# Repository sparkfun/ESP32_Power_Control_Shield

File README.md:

ESP32 Thing Power Control Shield
=======

*[SparkFun ESP32 Thing Power Control Shield](https://www.sparkfun.com/products/14155)*

The ESP32 Thing Power Control Shield is a small adapter board for the [ESP32 Thing](https://www.sparkfun.com/products/13907). The shield gives the ESP32 Thing the power to switch loads of up to 5A between 5 and 28VDC. The shield has 6 output pins to connect loads to, and three current sensors connected to outputs 2, 4, and 6. Operational amplifiers are by default configured as voltage followers, but feedback resistors are broken out to increase the gain of the non-inverting op-amp, which allows for greater precision depending on the maximum expected loads. 

Repository Contents
-------------------

* **/Production** - Panelized version of the design for production
* **/Hardware** - All Eagle design files (.brd, .sch)

License Information
-------------------

This design is [OSHW](http://www.oshwa.org/definition/) and public domain but you buy me a beer if you use this and we meet someday ([Beerware license](http://en.wikipedia.org/wiki/Beerware)).

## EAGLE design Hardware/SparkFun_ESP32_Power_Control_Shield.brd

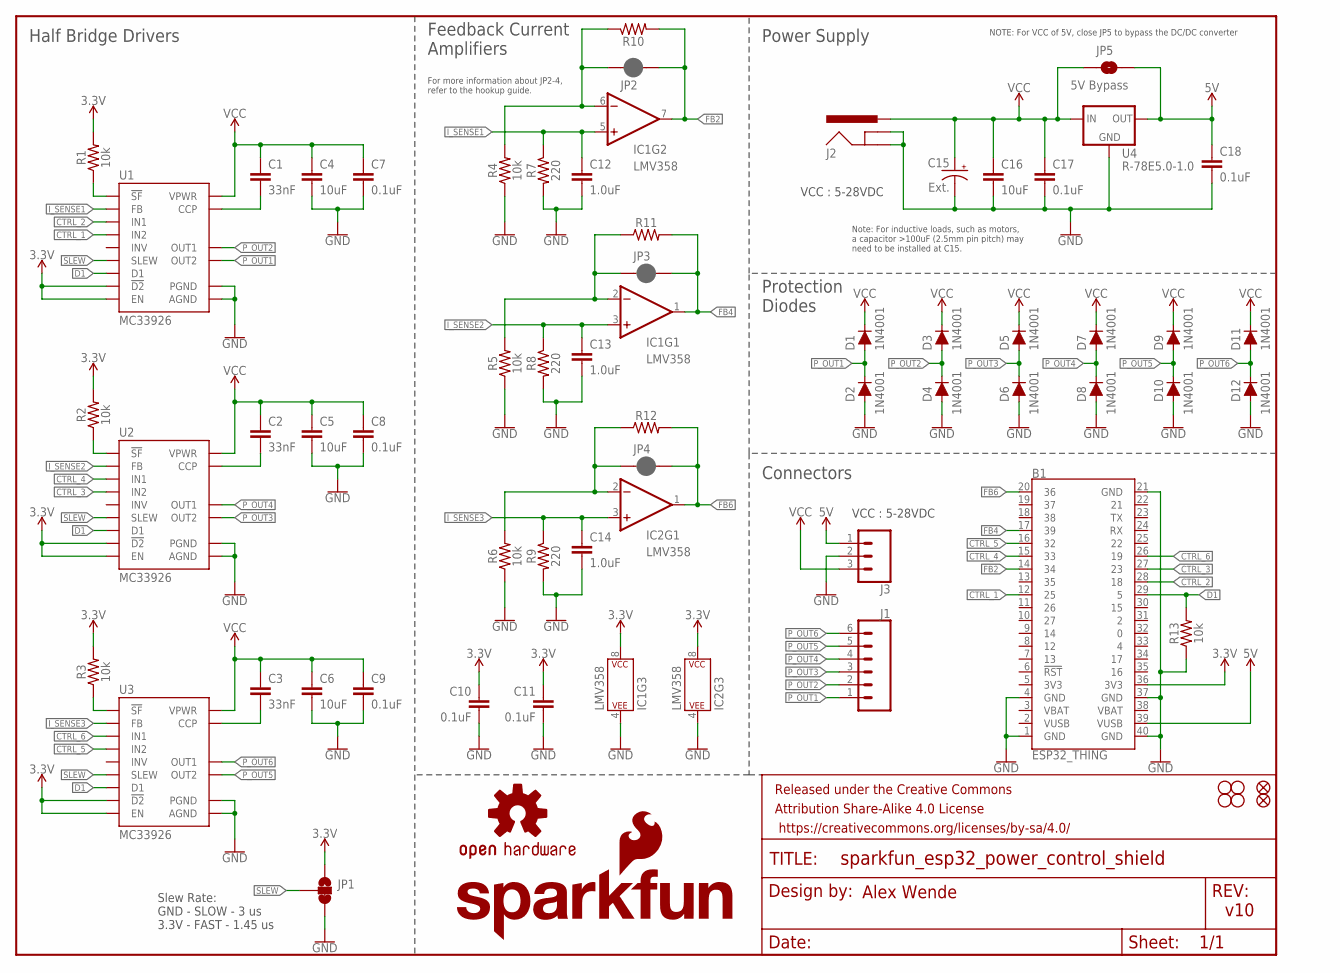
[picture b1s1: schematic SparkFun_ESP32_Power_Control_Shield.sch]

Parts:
B1: ESP32_THING
C1, C2, C3: 33nF; 0603
C4, C5, C6, C16: 10uF; 1210
C7, C8, C9, C10, C11, C17, C18: 0.1uF; 0603
C12, C13, C14: 1.0uF; 0603
C15: Ext.; CPOL-RADIAL-2.5MM-6.5MM
D1, D2, D3, D4, D5, D6, D7, D8, D9, D10, D11, D12: 1N4001; DIODE-1N4001
FD1, FD2: FIDUCIALUFIDUCIAL; FIDUCIAL-MICRO
FRAME1: FRAME-LETTER; CREATIVE_COMMONS
H1, H2, H3, H4: STAND-OFF
IC1, IC2: LMV358; SO08
J1: CONN_063.5MM-6; SCREWTERMINAL-3.5MM-6
J2: POWER_JACKPTH_LOCK; POWER_JACK_PTH_LOCK
J3: CONN_03SCREW; SCREWTERMINAL-3.5MM-3
JP1: JUMPER-SMT_3_1-NC_TRACE_SILK; SMT-JUMPER_3_1-NC_TRACE_SILK
JP2, JP3, JP4: JUMPER-SMT_2_NC_PASTE_NO-SILK; SMT-JUMPER_2_NC_PASTE_NO-SILK
JP5: 5V Bypass; SMT-JUMPER_2_NO_SILK
LOGO1: SFE_LOGO_NAME_FLAME.2_INCH; SFE_LOGO_NAME_FLAME_.2
LOGO2: OSHW-LOGOM; OSHW-LOGO-M
R1, R2, R3, R4, R5, R6, R13: 10k; 0603
R7, R8, R9: 220; 0603
R10, R11, R12: 1KOHM-HORIZ-1/4W-1%; AXIAL-0.3
U1, U2, U3: MC33926; 32-PQFN
U4: R-78E5.0-1.0; DC-DC_CONVERTER_78XX

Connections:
3.3V: B1.36 (3V3), C10.1, C11.1, IC1.8 (P$V+), IC2.8 (P$V+), JP1.1, R1.2, R2.2, R3.2, U1.P$10 (EN), U1.P$16 (!D2), U2.P$10 (EN), U2.P$16 (!D2), U3.P$10 (EN), U3.P$16 (!D2)
5V: B1.39 (VUSB), C18.1, J3.1, JP5.2, U4.VOUT (OUT)
CTRL_1: B1.12 (25), U1.P$1 (IN2)
CTRL_2: B1.28 (18), U1.P$2 (IN1)
CTRL_3: B1.27 (23), U2.P$1 (IN2)
CTRL_4: B1.15 (33), U2.P$2 (IN1)
CTRL_5: B1.16 (32), U3.P$1 (IN2)
CTRL_6: B1.26 (19), U3.P$2 (IN1)
D1: B1.29 (5), R13.2, U1.P$26 (D1), U2.P$26 (D1), U3.P$26 (D1)
FB2: B1.14 (34), IC1.7 (OUT), JP2.2, R10.P$2 (2)
FB4: B1.17 (39), IC1.1 (OUT), JP3.2, R11.P$2 (2)
FB6: B1.20 (36), IC2.1 (OUT), JP4.2, R12.P$2 (2)
GND: B1.1 (GND), B1.4 (GND), B1.21 (GND), B1.37 (GND), B1.40 (GND), C4.2, C5.2, C6.2, C7.2, C8.2, C9.2, C10.2, C11.2, C12.2, C13.2, C14.2, C15.2 (-), C16.2, C17.2, C18.2, D2.A, D4.A, D6.A, D8.A, D10.A, D12.A, IC1.4 (P$V-), IC2.4 (P$V-), J2.GND, J2.GNDBREAK, J3.2, JP1.3, R4.1, R5.1, R6.1, R7.2, R8.2, R9.2, R13.1, U1.P$5 (AGND), U1.P$18 (PGND), U1.P$19 (PGND), U1.P$20 (PGND), U1.P$22 (PGND), U1.P$23 (PGND), U1.P$24 (PGND), U1.P$33 (AGND), U2.P$5 (AGND), U2.P$18 (PGND), U2.P$19 (PGND), U2.P$20 (PGND), U2.P$22 (PGND), U2.P$23 (PGND), U2.P$24 (PGND), U2.P$33 (AGND), U3.P$5 (AGND), U3.P$18 (PGND), U3.P$19 (PGND), U3.P$20 (PGND), U3.P$22 (PGND), U3.P$23 (PGND), U3.P$24 (PGND), U3.P$33 (AGND), U4.GND
I_SENSE1: C12.1, IC1.5 (+IN), R7.1, U1.P$8 (FB)
I_SENSE2: C13.1, IC1.3 (+IN), R8.1, U2.P$8 (FB)
I_SENSE3: C14.1, IC2.3 (+IN), R9.1, U3.P$8 (FB)
unnamed: IC1.6 (-IN), JP2.1, R4.2, R10.P$1 (1)
unnamed: IC2.2 (-IN), JP4.1, R6.2, R12.P$1 (1)
unnamed: IC1.2 (-IN), JP3.1, R5.2, R11.P$1 (1)
unnamed: R2.1, U2.P$21 (!SF)
unnamed: C2.2, U2.P$32 (CCP)
unnamed: R3.1, U3.P$21 (!SF)
unnamed: R1.1, U1.P$21 (!SF)
unnamed: C1.2, U1.P$32 (CCP)
unnamed: C3.2, U3.P$32 (CCP)
P_OUT1: D1.A, D2.C, J1.1, U1.P$27 (OUT2), U1.P$28 (OUT2), U1.P$29 (OUT2), U1.P$30 (OUT2)
P_OUT2: D3.A, D4.C, J1.2, U1.P$12 (OUT1), U1.P$13 (OUT1), U1.P$14 (OUT1), U1.P$15 (OUT1)
P_OUT3: D5.A, D6.C, J1.3, U2.P$27 (OUT2), U2.P$28 (OUT2), U2.P$29 (OUT2), U2.P$30 (OUT2)
P_OUT4: D7.A, D8.C, J1.4, U2.P$12 (OUT1), U2.P$13 (OUT1), U2.P$14 (OUT1), U2.P$15 (OUT1)
P_OUT5: D9.A, D10.C, J1.5, U3.P$27 (OUT2), U3.P$28 (OUT2), U3.P$29 (OUT2), U3.P$30 (OUT2)
P_OUT6: D11.A, D12.C, J1.6, U3.P$12 (OUT1), U3.P$13 (OUT1), U3.P$14 (OUT1), U3.P$15 (OUT1)
SLEW: JP1.2, U1.P$3 (SLEW), U2.P$3 (SLEW), U3.P$3 (SLEW)
VCC: C1.1, C2.1, C3.1, C4.1, C5.1, C6.1, C7.1, C8.1, C9.1, C15.1 (+), C16.1, C17.1, D1.C, D3.C, D5.C, D7.C, D9.C, D11.C, J2.PWR, J3.3, JP5.1, U1.P$4 (VPWR), U1.P$6 (VPWR), U1.P$11 (VPWR), U1.P$31 (VPWR), U2.P$4 (VPWR), U2.P$6 (VPWR), U2.P$11 (VPWR), U2.P$31 (VPWR), U3.P$4 (VPWR), U3.P$6 (VPWR), U3.P$11 (VPWR), U3.P$31 (VPWR), U4.VIN (IN)

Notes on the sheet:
Alex Wende
v10
Half Bridge Drivers
Feedback Current Amplifiers
Power Supply
Protection Diodes
Connectors
Slew Rate: GND - SLOW - 3 us 3.3V - FAST - 1.45 us
VCC : 5-28VDC
NOTE: For VCC of 5V, close JP5 to bypass the DC/DC converter
For more information about JP2-4, refer to the hookup guide.
Note: For inductive loads, such as motors, a capacitor >100uF (2.5mm pin pitch) may need to be installed at C15.

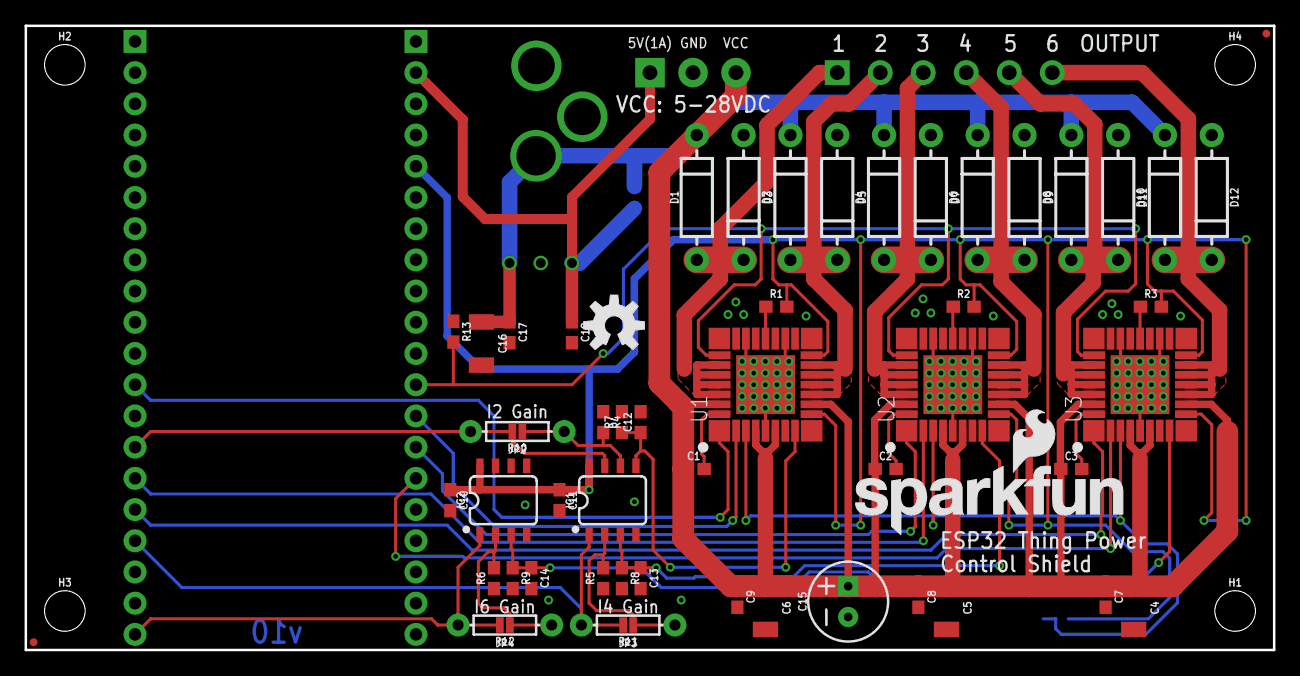
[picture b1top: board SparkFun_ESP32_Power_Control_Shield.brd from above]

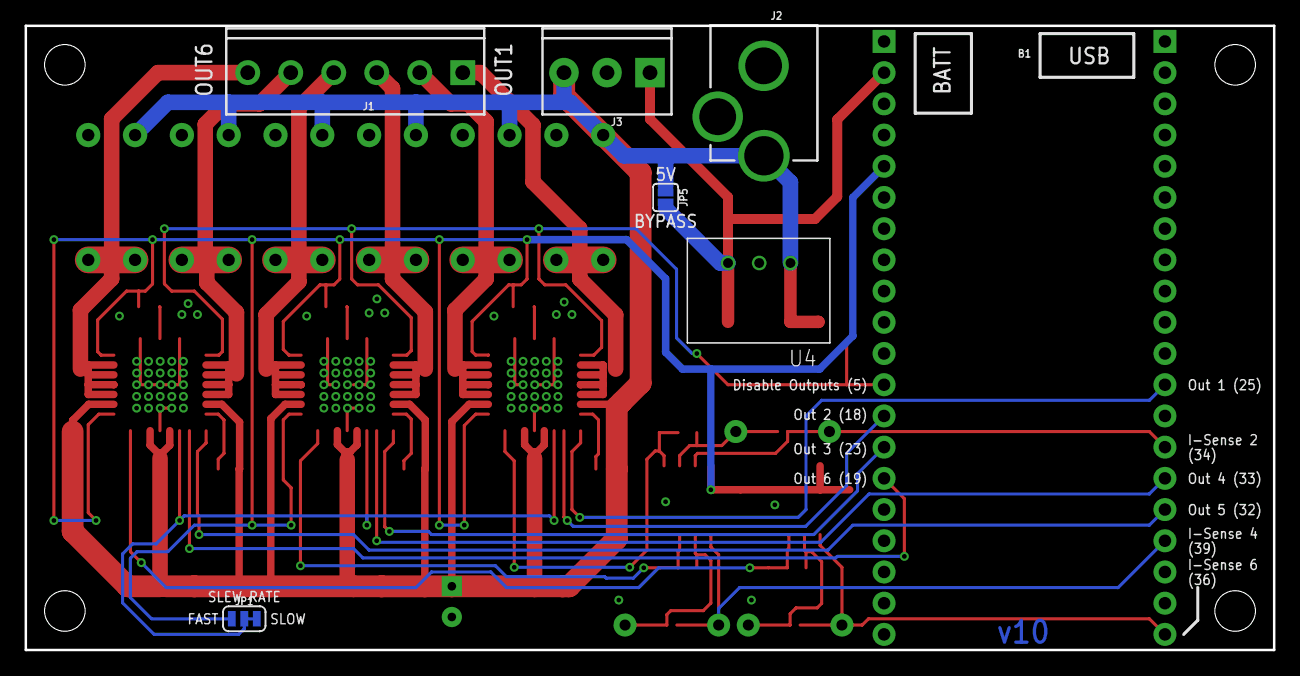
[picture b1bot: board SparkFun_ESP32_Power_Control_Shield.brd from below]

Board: 2 copper layers, 101.6 x 50.8 mm, 68 parts (7 on the bottom side), 33 nets.

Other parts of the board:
U$1: ORDERING_INSTRUCTIONS

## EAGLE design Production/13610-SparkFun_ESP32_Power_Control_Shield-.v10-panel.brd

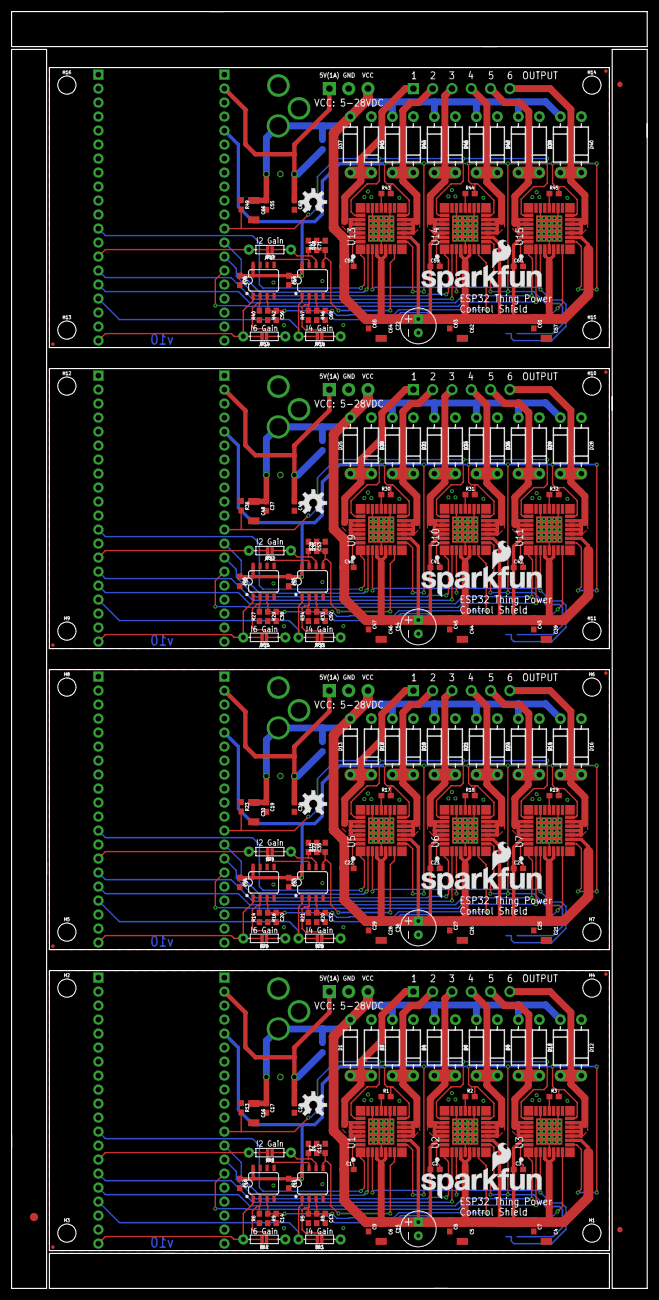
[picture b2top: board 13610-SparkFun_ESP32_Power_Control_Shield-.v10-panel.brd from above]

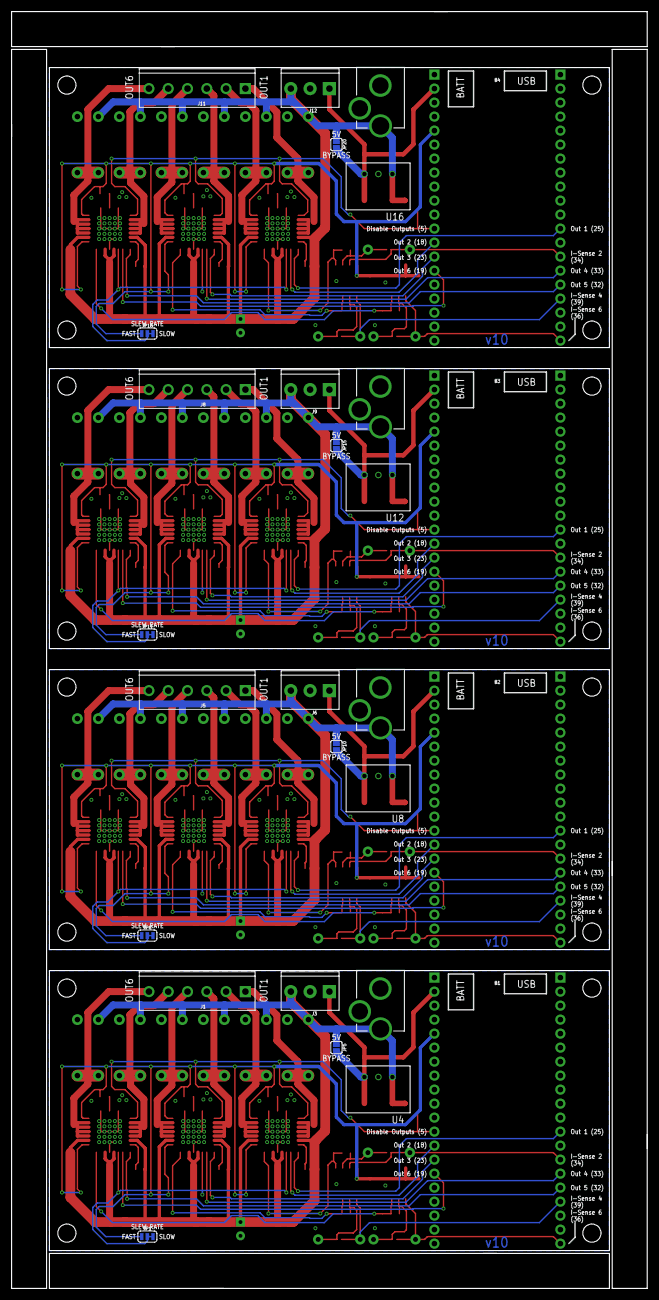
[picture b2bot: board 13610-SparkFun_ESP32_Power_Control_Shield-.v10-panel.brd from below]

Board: 2 copper layers, 115.3 x 231.6 mm, 267 parts (28 on the bottom side), 132 nets.

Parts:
B1, B2, B3, B4: ESP32_THING
C1, C2, C3, C22, C23, C24, C40, C41, C42, C58, C59, C60: 33nF; 0603
C4, C5, C6, C16, C21, C26, C28, C30, C39, C44, C46, C48, C57, C62, C64, C66: 10uF; 1210
C7, C8, C9, C10, C11, C17, C18, C19, C25, C27, C29, C31, C33, C34, C37, C43, C45, C47, C49, C51, C52, C55, C61, C63, C65, C67, C69, C70: 0.1uF; 0603
C12, C13, C14, C20, C32, C35, C38, C50, C53, C56, C68, C71: 1.0uF; 0603
C15, C36, C54, C72: Ext.; CPOL-RADIAL-2.5MM-6.5MM
D1, D2, D3, D4, D5, D6, D7, D8, D9, D10, D11, D12, D13, D14, D15, D16, D17, D18, D19, D20, D21, D22, D23, D24, D25, D26, D27, D28, D29, D30, D31, D32, D33, D34, D35, D36, D37, D38, D39, D40, D41, D42, D43, D44, D45, D46, D47, D48: 1N4001; DIODE-1N4001
E$1: FIDUCIAL-1.5X3
E$7, E$8: FIDUCIAL-1X2
FD1, FD2, FD3, FD4, FD5, FD6, FD7, FD8: FIDUCIALUFIDUCIAL; FIDUCIAL-MICRO
H1, H2, H3, H4, H5, H6, H7, H8, H9, H10, H11, H12, H13, H14, H15, H16: STAND-OFF
IC1, IC2, IC3, IC4, IC5, IC6, IC7, IC8: LMV358; SO08
J1, J5, J8, J11: SCREWTERMINAL-3.5MM-6
J2, J4, J7, J10: POWER_JACKPTH_LOCK; POWER_JACK_PTH_LOCK
J3, J6, J9, J12: SCREWTERMINAL-3.5MM-3
JP1, JP6, JP11, JP16: SMT-JUMPER_3_1-NC_TRACE_SILK
JP2, JP3, JP4, JP7, JP8, JP9, JP12, JP13, JP14, JP17, JP18, JP19: SMT-JUMPER_2_NC_PASTE_NO-SILK
JP5, JP10, JP15, JP20: 5V Bypass; SMT-JUMPER_2_NO_SILK
LOGO1, LOGO3, LOGO5, LOGO7: SFE_LOGO_NAME_FLAME.2_INCH; SFE_LOGO_NAME_FLAME_.2
LOGO2, LOGO4, LOGO6, LOGO8: OSHW-LOGOM; OSHW-LOGO-M
R1, R2, R3, R4, R5, R6, R13, R14, R17, R18, R19, R21, R22, R23, R27, R30, R31, R32, R34, R35, R36, R40, R43, R44, R45, R47, R48, R49: 10k; 0603
R7, R8, R9, R15, R16, R20, R28, R29, R33, R41, R42, R46: 220; 0603
R10, R11, R12, R24, R25, R26, R37, R38, R39, R50, R51, R52: AXIAL-0.3
U1, U2, U3, U5, U6, U7, U9, U10, U11, U13, U14, U15: MC33926; 32-PQFN
U4, U8, U12, U16: R-78E5.0-1.0; DC-DC_CONVERTER_78XX

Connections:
3.3V: B1.36, C10.1, C11.1, IC1.8, IC2.8, JP1.1, R1.2, R2.2, R3.2, U1.P$10, U1.P$16, U2.P$10, U2.P$16, U3.P$10, U3.P$16
3.3V1: B2.36, C33.1, C34.1, IC3.8, IC4.8, JP6.1, R17.2, R18.2, R19.2, U5.P$10, U5.P$16, U6.P$10, U6.P$16, U7.P$10, U7.P$16
3.3V2: B3.36, C51.1, C52.1, IC5.8, IC6.8, JP11.1, R30.2, R31.2, R32.2, U9.P$10, U9.P$16, U10.P$10, U10.P$16, U11.P$10, U11.P$16
3.3V3: B4.36, C69.1, C70.1, IC7.8, IC8.8, JP16.1, R43.2, R44.2, R45.2, U13.P$10, U13.P$16, U14.P$10, U14.P$16, U15.P$10, U15.P$16
5V: B1.39, C18.1, J3.1, JP5.2, U4.VOUT
5V1: B2.39, C31.1, J6.1, JP10.2, U8.VOUT
5V2: B3.39, C49.1, J9.1, JP15.2, U12.VOUT
5V3: B4.39, C67.1, J12.1, JP20.2, U16.VOUT
CTRL_1: B1.12, U1.P$1
CTRL_2: B1.28, U1.P$2
CTRL_3: B1.27, U2.P$1
CTRL_4: B1.15, U2.P$2
CTRL_5: B1.16, U3.P$1
CTRL_6: B1.26, U3.P$2
CTRL_7: B2.26, U7.P$2
CTRL_8: B2.16, U7.P$1
CTRL_9: B2.15, U6.P$2
CTRL_10: B2.27, U6.P$1
CTRL_11: B2.28, U5.P$2
CTRL_12: B2.12, U5.P$1
CTRL_13: B3.26, U11.P$2
CTRL_14: B3.16, U11.P$1
CTRL_15: B3.15, U10.P$2
CTRL_16: B3.27, U10.P$1
CTRL_17: B3.28, U9.P$2
CTRL_18: B3.12, U9.P$1
CTRL_19: B4.26, U15.P$2
CTRL_20: B4.16, U15.P$1
CTRL_21: B4.15, U14.P$2
CTRL_22: B4.27, U14.P$1
CTRL_23: B4.28, U13.P$2
CTRL_24: B4.12, U13.P$1
D1: B1.29, R13.2, U1.P$26, U2.P$26, U3.P$26
D2: B2.29, R23.2, U5.P$26, U6.P$26, U7.P$26
D3: B3.29, R36.2, U9.P$26, U10.P$26, U11.P$26
D4: B4.29, R49.2, U13.P$26, U14.P$26, U15.P$26
FB1: B2.20, IC4.1, JP9.2, R26.P$2
FB2: B1.14, IC1.7, JP2.2, R10.P$2
FB3: B2.17, IC3.1, JP8.2, R25.P$2
FB4: B1.17, IC1.1, JP3.2, R11.P$2
FB5: B2.14, IC3.7, JP7.2, R24.P$2
FB6: B1.20, IC2.1, JP4.2, R12.P$2
FB7: B3.20, IC6.1, JP14.2, R39.P$2
FB8: B3.17, IC5.1, JP13.2, R38.P$2
FB9: B3.14, IC5.7, JP12.2, R37.P$2
FB10: B4.20, IC8.1, JP19.2, R52.P$2
FB11: B4.17, IC7.1, JP18.2, R51.P$2
FB12: B4.14, IC7.7, JP17.2, R50.P$2
GND: B1.1, B1.4, B1.21, B1.37, B1.40, C4.2, C5.2, C6.2, C7.2, C8.2, C9.2, C10.2, C11.2, C12.2, C13.2, C14.2, C15.2, C16.2, C17.2, C18.2, D2.A, D4.A, D6.A, D8.A, D10.A, D12.A, IC1.4, IC2.4, J2.GND, J2.GNDBREAK, J3.2, JP1.3, R4.1, R5.1, R6.1, R7.2, R8.2, R9.2, R13.1, U1.P$5, U1.P$18, U1.P$19, U1.P$20, U1.P$22, U1.P$23, U1.P$24, U1.P$33, U2.P$5, U2.P$18, U2.P$19, U2.P$20, U2.P$22, U2.P$23, U2.P$24, U2.P$33, U3.P$5, U3.P$18, U3.P$19, U3.P$20, U3.P$22, U3.P$23, U3.P$24, U3.P$33, U4.GND
GND1: B2.1, B2.4, B2.21, B2.37, B2.40, C19.2, C20.2, C21.2, C25.2, C26.2, C27.2, C28.2, C29.2, C30.2, C31.2, C32.2, C33.2, C34.2, C35.2, C36.2, D14.A, D16.A, D17.A, D19.A, D21.A, D23.A, IC3.4, IC4.4, J4.GND, J4.GNDBREAK, J6.2, JP6.3, R14.1, R15.2, R16.2, R20.2, R21.1, R22.1, R23.1, U5.P$5, U5.P$18, U5.P$19, U5.P$20, U5.P$22, U5.P$23, U5.P$24, U5.P$33, U6.P$5, U6.P$18, U6.P$19, U6.P$20, U6.P$22, U6.P$23, U6.P$24, U6.P$33, U7.P$5, U7.P$18, U7.P$19, U7.P$20, U7.P$22, U7.P$23, U7.P$24, U7.P$33, U8.GND
GND2: B3.1, B3.4, B3.21, B3.37, B3.40, C37.2, C38.2, C39.2, C43.2, C44.2, C45.2, C46.2, C47.2, C48.2, C49.2, C50.2, C51.2, C52.2, C53.2, C54.2, D26.A, D28.A, D29.A, D31.A, D33.A, D35.A, IC5.4, IC6.4, J7.GND, J7.GNDBREAK, J9.2, JP11.3, R27.1, R28.2, R29.2, R33.2, R34.1, R35.1, R36.1, U9.P$5, U9.P$18, U9.P$19, U9.P$20, U9.P$22, U9.P$23, U9.P$24, U9.P$33, U10.P$5, U10.P$18, U10.P$19, U10.P$20, U10.P$22, U10.P$23, U10.P$24, U10.P$33, U11.P$5, U11.P$18, U11.P$19, U11.P$20, U11.P$22, U11.P$23, U11.P$24, U11.P$33, U12.GND
GND3: B4.1, B4.4, B4.21, B4.37, B4.40, C55.2, C56.2, C57.2, C61.2, C62.2, C63.2, C64.2, C65.2, C66.2, C67.2, C68.2, C69.2, C70.2, C71.2, C72.2, D38.A, D40.A, D41.A, D43.A, D45.A, D47.A, IC7.4, IC8.4, J10.GND, J10.GNDBREAK, J12.2, JP16.3, R40.1, R41.2, R42.2, R46.2, R47.1, R48.1, R49.1, U13.P$5, U13.P$18, U13.P$19, U13.P$20, U13.P$22, U13.P$23, U13.P$24, U13.P$33, U14.P$5, U14.P$18, U14.P$19, U14.P$20, U14.P$22, U14.P$23, U14.P$24, U14.P$33, U15.P$5, U15.P$18, U15.P$19, U15.P$20, U15.P$22, U15.P$23, U15.P$24, U15.P$33, U16.GND
I_SENSE1: C12.1, IC1.5, R7.1, U1.P$8
I_SENSE2: C13.1, IC1.3, R8.1, U2.P$8
I_SENSE3: C14.1, IC2.3, R9.1, U3.P$8
I_SENSE4: C35.1, IC3.5, R15.1, U5.P$8
I_SENSE5: C32.1, IC3.3, R20.1, U6.P$8
I_SENSE6: C20.1, IC4.3, R16.1, U7.P$8
I_SENSE7: C53.1, IC5.5, R28.1, U9.P$8
I_SENSE8: C50.1, IC5.3, R33.1, U10.P$8
I_SENSE9: C38.1, IC6.3, R29.1, U11.P$8
I_SENSE10: C71.1, IC7.5, R41.1, U13.P$8
I_SENSE11: C68.1, IC7.3, R46.1, U14.P$8
I_SENSE12: C56.1, IC8.3, R42.1, U15.P$8
unnamed: R17.1, U5.P$21
unnamed: IC1.6, JP2.1, R4.2, R10.P$1
unnamed: C22.2, U5.P$32
unnamed: IC2.2, JP4.1, R6.2, R12.P$1
unnamed: IC1.2, JP3.1, R5.2, R11.P$1
unnamed: R2.1, U2.P$21
unnamed: C2.2, U2.P$32
unnamed: R18.1, U6.P$21
unnamed: R3.1, U3.P$21
unnamed: R1.1, U1.P$21
unnamed: C1.2, U1.P$32
unnamed: C3.2, U3.P$32
unnamed: C23.2, U6.P$32
unnamed: R19.1, U7.P$21
unnamed: C24.2, U7.P$32
unnamed: IC3.2, JP8.1, R21.2, R25.P$1
unnamed: IC3.6, JP7.1, R22.2, R24.P$1
unnamed: IC4.2, JP9.1, R14.2, R26.P$1
unnamed: R30.1, U9.P$21
unnamed: C40.2, U9.P$32
unnamed: R31.1, U10.P$21
unnamed: C41.2, U10.P$32
unnamed: R32.1, U11.P$21
unnamed: C42.2, U11.P$32
unnamed: IC5.2, JP13.1, R34.2, R38.P$1
unnamed: IC5.6, JP12.1, R35.2, R37.P$1
unnamed: IC6.2, JP14.1, R27.2, R39.P$1
unnamed: R43.1, U13.P$21
unnamed: C58.2, U13.P$32
unnamed: R44.1, U14.P$21
unnamed: C59.2, U14.P$32
unnamed: R45.1, U15.P$21
unnamed: C60.2, U15.P$32
unnamed: IC7.2, JP18.1, R47.2, R51.P$1
unnamed: IC7.6, JP17.1, R48.2, R50.P$1
unnamed: IC8.2, JP19.1, R40.2, R52.P$1
P_OUT1: D1.A, D2.C, J1.1, U1.P$27, U1.P$28, U1.P$29, U1.P$30
P_OUT2: D3.A, D4.C, J1.2, U1.P$12, U1.P$13, U1.P$14, U1.P$15
P_OUT3: D5.A, D6.C, J1.3, U2.P$27, U2.P$28, U2.P$29, U2.P$30
P_OUT4: D7.A, D8.C, J1.4, U2.P$12, U2.P$13, U2.P$14, U2.P$15
P_OUT5: D9.A, D10.C, J1.5, U3.P$27, U3.P$28, U3.P$29, U3.P$30
P_OUT6: D11.A, D12.C, J1.6, U3.P$12, U3.P$13, U3.P$14, U3.P$15
P_OUT7: D18.A, D19.C, J5.2, U5.P$12, U5.P$13, U5.P$14, U5.P$15
P_OUT8: D22.A, D23.C, J5.4, U6.P$12, U6.P$13, U6.P$14, U6.P$15
P_OUT9: D15.A, D16.C, J5.6, U7.P$12, U7.P$13, U7.P$14, U7.P$15
P_OUT10: D13.A, D17.C, J5.1, U5.P$27, U5.P$28, U5.P$29, U5.P$30
P_OUT11: D14.C, D24.A, J5.5, U7.P$27, U7.P$28, U7.P$29, U7.P$30
P_OUT12: D20.A, D21.C, J5.3, U6.P$27, U6.P$28, U6.P$29, U6.P$30
P_OUT13: D30.A, D31.C, J8.2, U9.P$12, U9.P$13, U9.P$14, U9.P$15
P_OUT14: D34.A, D35.C, J8.4, U10.P$12, U10.P$13, U10.P$14, U10.P$15
P_OUT15: D27.A, D28.C, J8.6, U11.P$12, U11.P$13, U11.P$14, U11.P$15
P_OUT16: D25.A, D29.C, J8.1, U9.P$27, U9.P$28, U9.P$29, U9.P$30
P_OUT17: D26.C, D36.A, J8.5, U11.P$27, U11.P$28, U11.P$29, U11.P$30
P_OUT18: D32.A, D33.C, J8.3, U10.P$27, U10.P$28, U10.P$29, U10.P$30
P_OUT19: D42.A, D43.C, J11.2, U13.P$12, U13.P$13, U13.P$14, U13.P$15
P_OUT20: D46.A, D47.C, J11.4, U14.P$12, U14.P$13, U14.P$14, U14.P$15
P_OUT21: D39.A, D40.C, J11.6, U15.P$12, U15.P$13, U15.P$14, U15.P$15
P_OUT22: D37.A, D41.C, J11.1, U13.P$27, U13.P$28, U13.P$29, U13.P$30
P_OUT23: D38.C, D48.A, J11.5, U15.P$27, U15.P$28, U15.P$29, U15.P$30
P_OUT24: D44.A, D45.C, J11.3, U14.P$27, U14.P$28, U14.P$29, U14.P$30
SLEW: JP1.2, U1.P$3, U2.P$3, U3.P$3
SLEW1: JP6.2, U5.P$3, U6.P$3, U7.P$3
SLEW2: JP11.2, U9.P$3, U10.P$3, U11.P$3
SLEW3: JP16.2, U13.P$3, U14.P$3, U15.P$3
VCC: C1.1, C2.1, C3.1, C4.1, C5.1, C6.1, C7.1, C8.1, C9.1, C15.1, C16.1, C17.1, D1.C, D3.C, D5.C, D7.C, D9.C, D11.C, J2.PWR, J3.3, JP5.1, U1.P$4, U1.P$6, U1.P$11, U1.P$31, U2.P$4, U2.P$6, U2.P$11, U2.P$31, U3.P$4, U3.P$6, U3.P$11, U3.P$31, U4.VIN
VCC1: C19.1, C21.1, C22.1, C23.1, C24.1, C25.1, C26.1, C27.1, C28.1, C29.1, C30.1, C36.1, D13.C, D15.C, D18.C, D20.C, D22.C, D24.C, J4.PWR, J6.3, JP10.1, U5.P$4, U5.P$6, U5.P$11, U5.P$31, U6.P$4, U6.P$6, U6.P$11, U6.P$31, U7.P$4, U7.P$6, U7.P$11, U7.P$31, U8.VIN
VCC2: C37.1, C39.1, C40.1, C41.1, C42.1, C43.1, C44.1, C45.1, C46.1, C47.1, C48.1, C54.1, D25.C, D27.C, D30.C, D32.C, D34.C, D36.C, J7.PWR, J9.3, JP15.1, U9.P$4, U9.P$6, U9.P$11, U9.P$31, U10.P$4, U10.P$6, U10.P$11, U10.P$31, U11.P$4, U11.P$6, U11.P$11, U11.P$31, U12.VIN
VCC3: C55.1, C57.1, C58.1, C59.1, C60.1, C61.1, C62.1, C63.1, C64.1, C65.1, C66.1, C72.1, D37.C, D39.C, D42.C, D44.C, D46.C, D48.C, J10.PWR, J12.3, JP20.1, U13.P$4, U13.P$6, U13.P$11, U13.P$31, U14.P$4, U14.P$6, U14.P$11, U14.P$31, U15.P$4, U15.P$6, U15.P$11, U15.P$31, U16.VIN

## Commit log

2017-01-30 Initial Commit
    Initial layout for the SparkFun ESP32 Thing Power Control Shield.
2017-01-30 Added measurements for board size and version number
2017-01-30 Added external capacitor
    External capacitor will be populated by end user if too much ripple is
    present on power rail.
2017-02-01 Proto design review changes
    - Replaced SMD barrel jack with PTH
    - Replaced op-amp resistor with 15k resistor
    - Moved IO away from pins 34-39
    - Attached disable input pin to IO pin
    - Replaced 3/4 2-pin screw terminals with 6-pin screw terminal
    - Added labeling to all IO pins used
2017-02-01 Same changes as design review
    Forgot to save changes before commit.
2017-02-01 QC Fixes
    Replaced 0.1uF capacitors CAP-00810 with CAP-08390
2017-03-08 v10 Changes
    - Flipped connectors from top layer to bottom
    - Replaced 2-pin power connector with a 3-pin. Additional pin breaks out
    5V power rail for a 5VDC fan.
    - Added pull-down resistor to disable output (enabled by default).
    - Replaced 5V LDO with DC/DC converter
    - Replaced 240ohm resistors with 220ohm
2017-03-10 v10 changes additional
    minor schematic layout changes, added values for the op-amps and diodes.
2017-03-10 Added PROD_ID to DC/DC Converter
2017-03-22 panel
2017-05-19 Replaced R13
    Pull down resistor R13 was too weak for the ESP32 at 10k. Replacing with
    1k.
2017-06-09 Fixed words in readme

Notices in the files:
parts and their libraries:
SparkFun-Capacitors: Licensing: Creative Commons ShareAlike 4.0 International - https://creativecommons.org/licenses/by-sa/4.0
SparkFun-Aesthetics: Released under the Creative Commons Attribution Share-Alike 4.0 License
SparkFun-Aesthetics: https://creativecommons.org/licenses/by-sa/4.0
